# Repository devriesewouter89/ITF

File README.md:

# ITF

Includes illustrator file for lasercutting pillars made in 7mm multiplex wood
Includes Eagle drawings for PCB design with arduino incorporated to be able to switch 230VAC (optocoupler based)
Includes lasercuttable models used on ITF Flanders 2017
Includes Arduino code to fetch airquality data of BelAir project to alter color of ledstrips at foot of pillar (! not ready yet)

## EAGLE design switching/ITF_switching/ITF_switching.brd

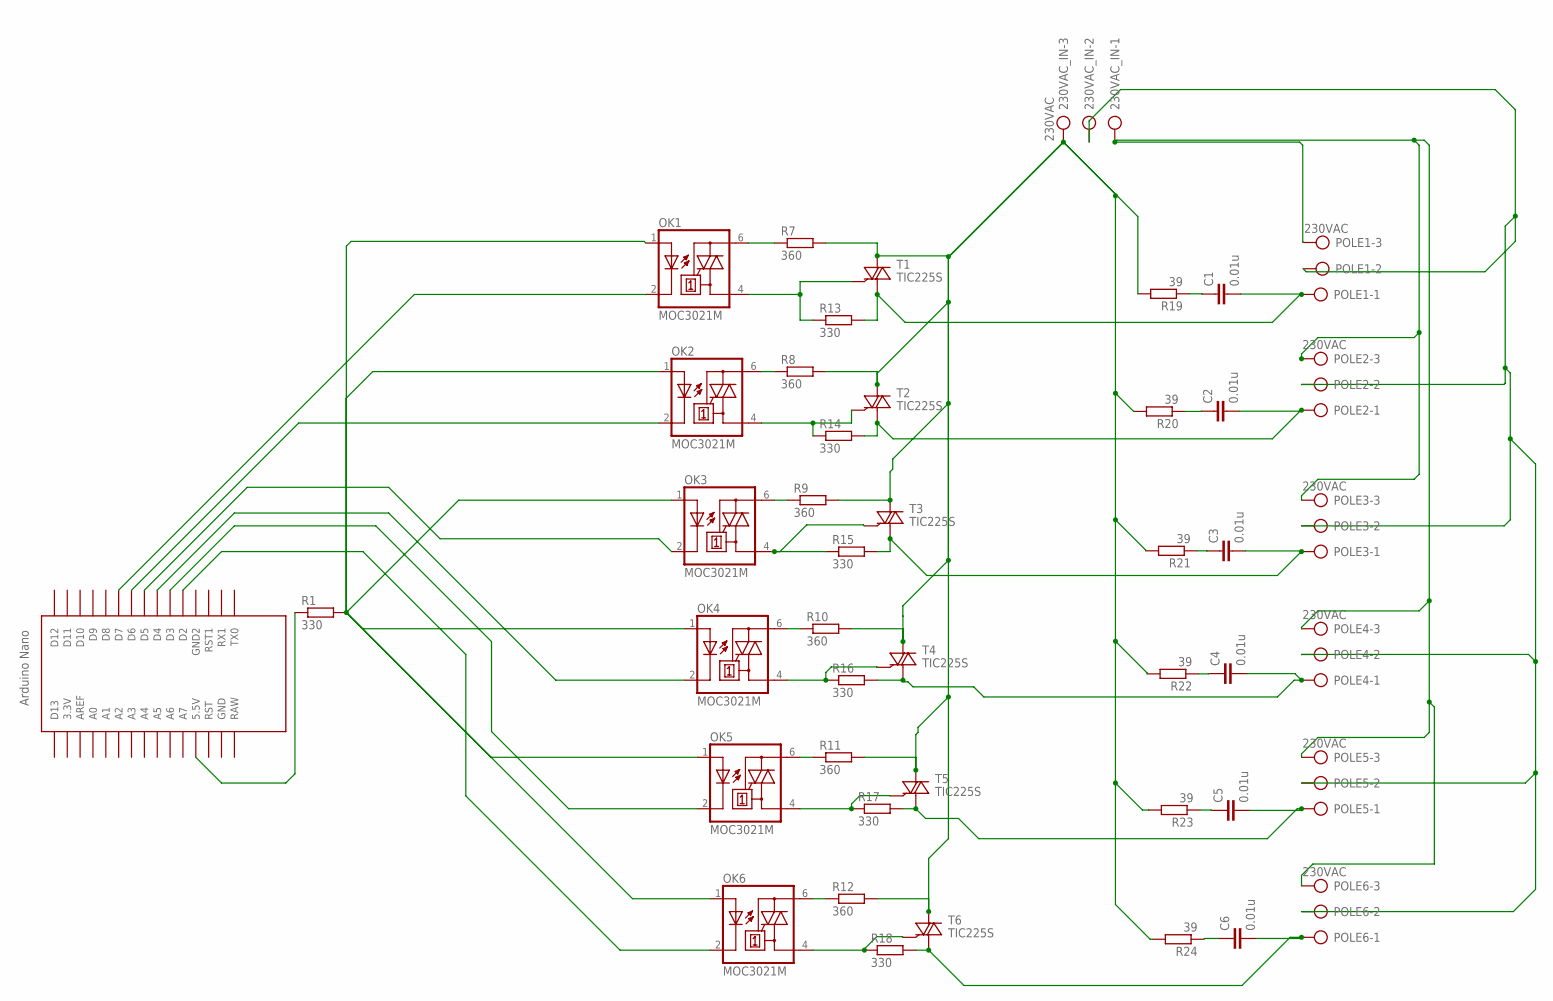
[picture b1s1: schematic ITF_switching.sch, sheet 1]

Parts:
230VAC_IN: 230VAC; AK300/3
C1, C2, C3, C4, C5, C6: 0.01u; C2.5-6
OK1, OK2, OK3, OK4, OK5, OK6: MOC3021M; DIL06
POLE1, POLE2, POLE3, POLE4, POLE5, POLE6: 230VAC; AK300/3
R1, R13, R14, R15, R16, R17, R18: 330; 0207/10
R7, R8, R9, R10, R11, R12: 360; 0207/10
R19, R20, R21, R22, R23, R24: 39; 0207/10
T1, T2, T3, T4, T5, T6: TIC225S; TO220DS
U$1: NANO

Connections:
unnamed: R1.1, U$1.5V (5.5V)
unnamed: OK1.1 (A), OK2.1 (A), OK3.1 (A), OK4.1 (A), OK5.1 (A), OK6.1 (A), R1.2
unnamed: OK6.2 (C), U$1.D2
unnamed: OK5.2 (C), U$1.D3
unnamed: OK4.2 (C), U$1.D4
unnamed: OK3.2 (C), U$1.D5
unnamed: OK2.2 (C), U$1.D6
unnamed: OK1.2 (C), U$1.D7
unnamed: OK1.6 (A2), R7.1
unnamed: 230VAC_IN.1, POLE1.3, POLE2.3, POLE3.3, POLE4.3, POLE5.3, POLE6.3
unnamed: OK2.6 (A2), R8.1
unnamed: C3.1, R21.1
unnamed: OK3.6 (A2), R9.1
unnamed: OK3.4 (A1), R15.1, T3.G
unnamed: OK4.6 (A2), R10.1
unnamed: C1.2, POLE1.1, R13.2, T1.A1
unnamed: OK5.6 (A2), R11.1
unnamed: C2.2, POLE2.1, R14.2, T2.A1
unnamed: OK6.6 (A2), R12.1
unnamed: C3.2, POLE3.1, R15.2, T3.A1
unnamed: OK2.4 (A1), R14.1, T2.G
unnamed: OK1.4 (A1), R13.1, T1.G
unnamed: OK4.4 (A1), R16.1, T4.G
unnamed: OK5.4 (A1), R17.1, T5.G
unnamed: OK6.4 (A1), R18.1, T6.G
unnamed: C4.2, POLE4.1, R16.2, T4.A1
unnamed: C6.1, R24.1
unnamed: C5.1, R23.1
unnamed: C4.1, R22.1
unnamed: C2.1, R20.1
unnamed: 230VAC_IN.3, R7.2, R8.2, R9.2, R10.2, R11.2, R12.2, R19.2, R20.2, R21.2, R22.2, R23.2, R24.2, T1.A2, T2.A2, T3.A2, T4.A2, T5.A2, T6.A2
unnamed: C1.1, R19.1
unnamed: C5.2, POLE5.1, R17.2, T5.A1
unnamed: 230VAC_IN.2, POLE1.2, POLE2.2, POLE3.2, POLE4.2, POLE5.2, POLE6.2
unnamed: C6.2, POLE6.1, R18.2, T6.A1

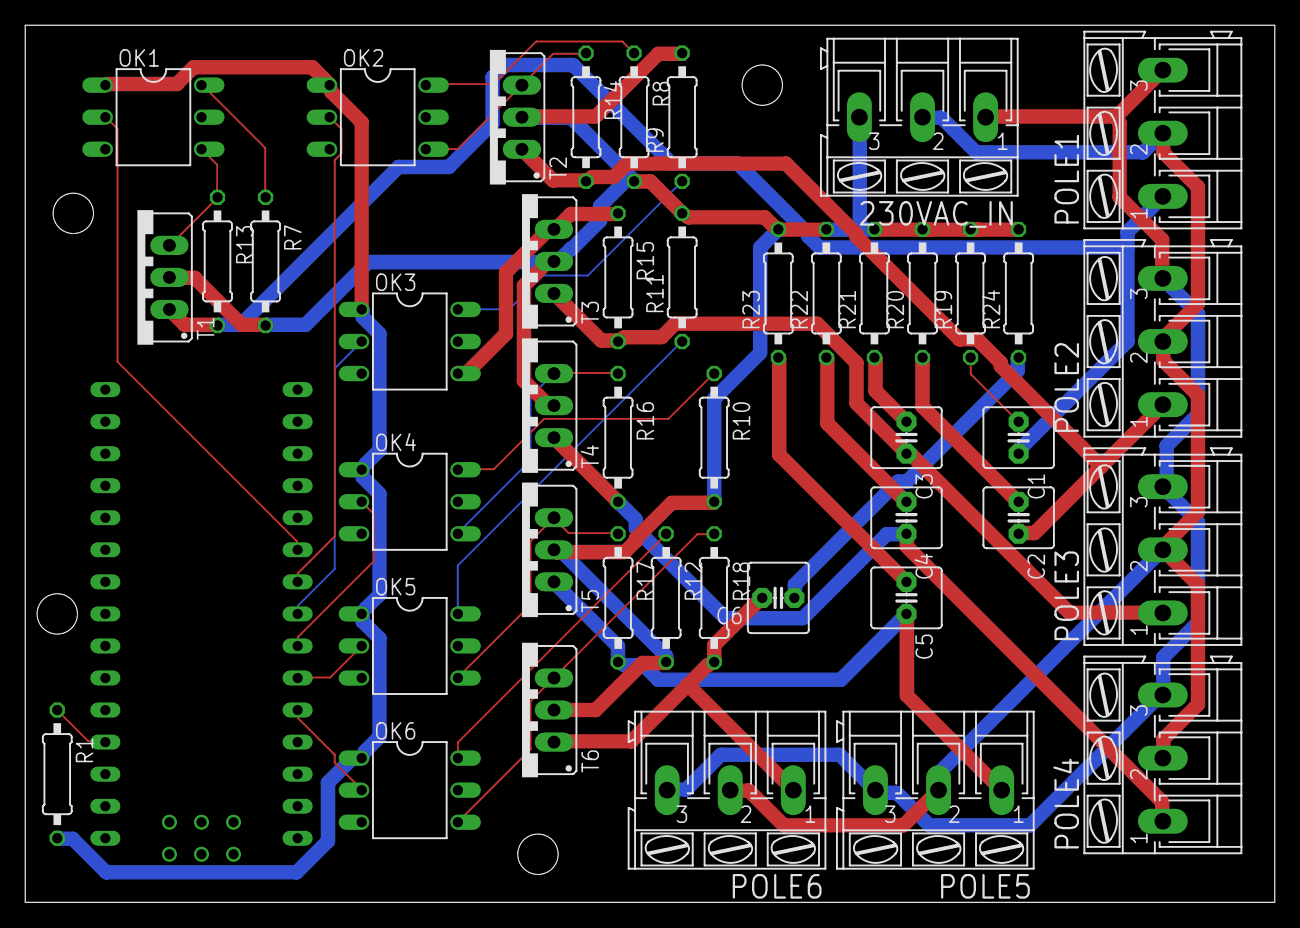
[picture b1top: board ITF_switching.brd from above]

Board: 2 copper layers, 99.0 x 69.5 mm, 45 parts (0 on the bottom side), 35 nets.

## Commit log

2017-07-11 added final used files
